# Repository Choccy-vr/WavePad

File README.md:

# WavePad

### Meet WavePad, the ultimate desktop companion.

With inspiration from the Stream Deck, this can do a whole load of things like opening an app, checking system vitals, along with many more things, such as controlling music, focus, etc. You can even create your own app! The possibilities are endless.

### So, how do you control this?

You can do all those things listed above and more, all with a variety of hand gestures or by interacting with a touch screen. By using an IR camera, WavePad can dectect hand gestures even in the dark!

### Features

- All off-the-shelf parts (Except the PCB)

- Gesture Detection (Hand and some finger tracking)

- Built on Raspberry Pi OS 

- Custom Apps (You can build them yourself!)

- Touch Screen

- PC Communication (Acting like a Stream Deck)

- Standalone Operation
  
- More To Come

### BOM

| Item Name    | Purpose           | Source                                                 | Price | Total |
| ------------ | ----------------- | ------------------------------------------------------ | ----- | ----- |
| CM4 1GB Lite | Main Compute Unit | https://www.mouser.com/ProductDetail/358-SC0691        | $35$  |       |
| 4.3in QLED   | Display           | https://www.waveshare.com/43h-800480-ips.htm?sku=24774 | $40$  |       |
| NoIR Camera  | Gesture           | https://www.mouser.com/ProductDetail/358-SC0024        | $15$  |       |
|              |                   |                                                        |       |       |
|              |                   |                                                        |       |       |

## Work in Progress

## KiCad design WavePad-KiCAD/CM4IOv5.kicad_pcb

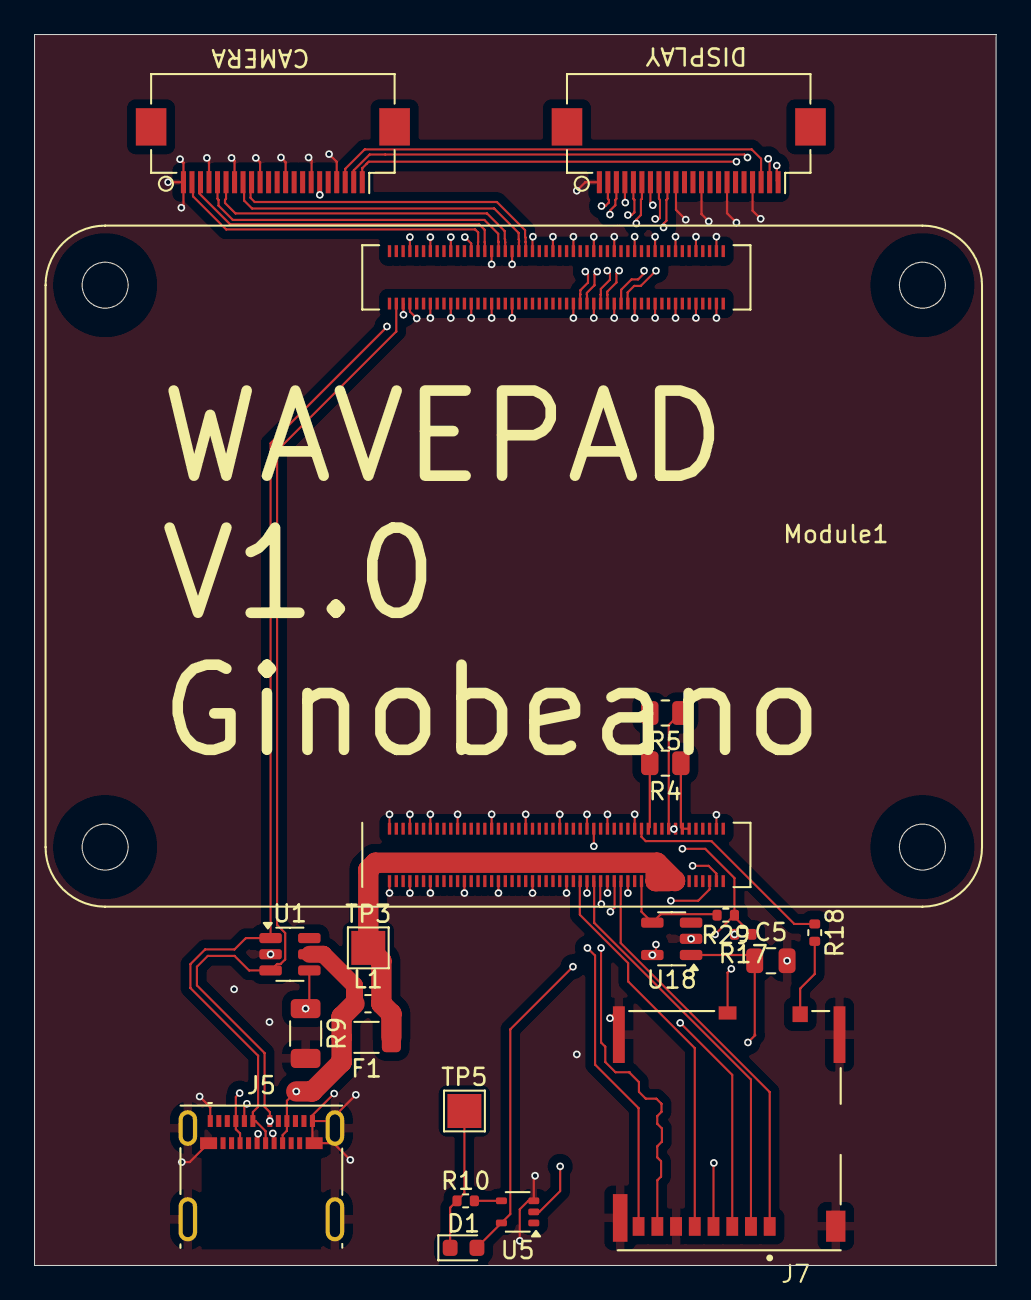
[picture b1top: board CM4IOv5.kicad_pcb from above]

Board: 4 copper layers, 56.5 x 72.3 mm, 21 parts (0 on the bottom side), 39 nets.

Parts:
C5: 10u; C_0805_2012Metric
D1: LED Red; LED_0603_1608Metric
F1: PTC Fuse; R_1206_3216Metric
J5: USB_C_Receptacle_USB2.0_14P; USB_C_Receptacle_Molex_105450-0101
J7: Micro_SD_Card_Det; SDCARD_MOLEX_503398-1892
J8, J15: Conn_01x22_Female; Hirose_FH12-22S-0.5SH_1x22-1MP_P0.50mm_Horizontal
L1: L; L_0603_1608Metric
Module1: ComputeModule4; Raspberry-Pi-4-Compute-Module
R4: nf; R_0805_2012Metric
R5: 0R; R_0805_2012Metric
R9: 5.1K; R_1206_3216Metric
R10: 1k; R_0402_1005Metric
R17, R18: nf; R_0402_1005Metric
R29: 12K 1%; R_0402_1005Metric
TP3: USB 5v; TestPoint_Pad_2.0x2.0mm
TP5: TestPoint; TestPoint_Pad_2.0x2.0mm
U1: USBLC6-4SC6; SOT-23-6
U5: 74LVC1G07SE-7; SOT-353_SC-70-5
U18: RT9742GGJ5; SOT-23-5

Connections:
/+3.3v: D1.2 (A), Module1.84 (+3.3v_(Output)), Module1.86 (+3.3v_(Output)), R5.1, R17.1, R29.1, U5.5 (VCC), U18.5 (IN)
/+5v: F1.1, L1.2, Module1.77 (+5v_(Input)), Module1.79 (+5v_(Input)), Module1.81 (+5v_(Input)), Module1.83 (+5v_(Input)), Module1.85 (+5v_(Input)), Module1.87 (+5v_(Input)), TP3.1
/CM4_GPIO (GPIO, SDCARD)/+1.8v: Module1.88 (+1.8v_(Output)), Module1.90 (+1.8v_(Output)), R4.1
/CM4_GPIO (GPIO, SDCARD)/GPIO_VREF: Module1.78 (GPIO_VREF(1.8v/3.3v_Input)), R4.2, R5.2
/CM4_GPIO (GPIO, SDCARD)/Reserved: Module1.76 (Reserved), R18.1
/CM4_GPIO (GPIO, SDCARD)/SD_CLK: J7.5 (CLK), Module1.57 (SD_CLK)
/CM4_GPIO (GPIO, SDCARD)/SD_CMD: J7.3 (CMD), Module1.62 (SD_CMD)
/CM4_GPIO (GPIO, SDCARD)/SD_DAT0: J7.7 (DAT0), Module1.63 (SD_DAT0)
/CM4_GPIO (GPIO, SDCARD)/SD_DAT1: J7.8 (DAT1), Module1.67 (SD_DAT1)
/CM4_GPIO (GPIO, SDCARD)/SD_DAT2: J7.1 (DAT2), Module1.69 (SD_DAT2)
/CM4_GPIO (GPIO, SDCARD)/SD_DAT3: J7.2 (DAT3/CD), Module1.61 (SD_DAT3)
/CM4_GPIO (GPIO, SDCARD)/SD_PWR: C5.1, J7.4 (VDD), U18.1 (OUT)
/CM4_GPIO (GPIO, SDCARD)/SD_PWR_ON: Module1.75 (SD_PWR_ON), R29.2, U18.4 (EN)
/CM4_GPIO (GPIO, SDCARD)/nPWR_LED: Module1.95 (nPI_LED_PWR), U5.2
/CM4_HighSpeed/+3.3v: J8.22, J15.22
/CM4_HighSpeed/CAM0_C_N: J8.8, Module1.140 (CAM0_C_N)
/CM4_HighSpeed/CAM0_C_P: J8.9, Module1.142 (CAM0_C_P)
/CM4_HighSpeed/CAM0_D0_N: J8.2, Module1.128 (CAM0_D0_N)
/CM4_HighSpeed/CAM0_D0_P: J8.3, Module1.130 (CAM0_D0_P)
/CM4_HighSpeed/CAM0_D1_N: J8.5, Module1.134 (CAM0_D1_N)
/CM4_HighSpeed/CAM0_D1_P: J8.6, Module1.136 (CAM0_D1_P)
/CM4_HighSpeed/CAM_GPIO: J8.17, Module1.97 (Camera_GPIO)
/CM4_HighSpeed/DSI0_C_N: J15.8, Module1.169 (DSI0_C_N)
/CM4_HighSpeed/DSI0_C_P: J15.9, Module1.171 (DSI0_C_P)
/CM4_HighSpeed/DSI0_D0_N: J15.2, Module1.157 (DSI0_D0_N)
/CM4_HighSpeed/DSI0_D0_P: J15.3, Module1.159 (DSI0_D0_P)
/CM4_HighSpeed/DSI0_D1_N: J15.5, Module1.163 (DSI0_D1_N)
/CM4_HighSpeed/DSI0_D1_P: J15.6, Module1.165 (DSI0_D1_P)
/CM4_HighSpeed/SCL1: J8.20, J15.20
/CM4_HighSpeed/SDA1: J8.21, J15.21
/USB/USB D+: J5.A6 (D+), J5.B6 (D+), Module1.105 (USB2_P), U1.1 (I/O1)
/USB/USB D-: J5.A7 (D-), J5.B7 (D-), Module1.103 (USB2_N), U1.3 (I/O2)
GND: C5.2, J5.A1 (GND), J5.A12 (GND), J5.B1 (GND), J5.B12 (GND), J5.S1 (SHIELD), J7.6 (VSS), J7.11 (SHIELD), J8.1, J8.4, J8.7, J8.10, J8.13, J8.16, J8.19, J15.1, J15.4, J15.7, J15.10, J15.13, J15.16, J15.19, Module1.1 (GND), Module1.2 (GND), Module1.7 (GND), Module1.8 (GND), Module1.13 (GND), Module1.14 (GND), Module1.22 (GND), Module1.23 (GND), Module1.32 (GND), Module1.33 (GND), Module1.42 (GND), Module1.43 (GND), Module1.52 (GND), Module1.53 (GND), Module1.59 (GND), Module1.60 (GND), Module1.65 (GND), Module1.66 (GND), Module1.71 (GND), Module1.74 (GND), Module1.98 (GND), Module1.107 (GND), Module1.108 (GND), Module1.113 (GND), Module1.114 (GND), Module1.119 (GND), Module1.120 (GND), Module1.125 (GND), Module1.126 (GND), Module1.131 (GND), Module1.132 (GND), Module1.137 (GND), Module1.138 (GND), Module1.144 (GND), Module1.150 (GND), Module1.155 (GND), Module1.156 (GND), Module1.161 (GND), Module1.162 (GND), Module1.167 (GND), Module1.168 (GND), Module1.173 (GND), Module1.174 (GND), Module1.179 (GND), Module1.180 (GND), Module1.185 (GND), Module1.186 (GND), Module1.191 (GND), Module1.192 (GND), Module1.197 (GND), Module1.198 (GND), R9.2, U1.2 (GND), U5.3 (GND), U18.2 (GND)
unnamed: D1.1 (K), R10.1, TP5.1
unnamed: J5.A5 (CC1), J5.B5 (CC2), R9.1, U1.4 (I/O3)
unnamed: J7.10 (DET_A), R17.2
unnamed: J7.9 (DET_B), R18.2
unnamed: R10.2, U5.4
unnamed: F1.2, J5.A4 (VBUS), J5.A9 (VBUS), J5.B4 (VBUS), J5.B9 (VBUS), L1.1, U1.5 (VBUS)

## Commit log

2025-05-23 Initial Commit
    Add Journal and README
2025-05-23 Add Schematic/PCB Files
    Adapted off of CM4IO Board Template
2025-05-23 Started PCB
    Added CSI and DSI connector as well as a USB C with protected data and Power
2025-05-24 Worked on PCB
    Almost finished the PCB
2025-05-26 Base OS
2025-05-26 Update JOURNAL.md
    5/26
2025-05-28 Fixed OS
2025-06-04 Finish PCB Design
2025-06-04 Specify Serial-Number placement
2025-06-17 Home Screen Layout
2025-06-17 Apps Screen
2025-06-18 Fix Navigation Bug
2025-06-20 Apps
2025-06-21 SQLite Manager
2025-06-23 Pipes
2025-06-23 Pipes & JSON
2025-06-23 Run Pipes and Remove Setup
2025-06-23 Building
2025-06-26 Weather
2025-06-27 Weather service
2025-06-28 Weather UI
2025-06-30 Weather - Home Page
2025-07-02 Weather Details
2025-07-02 Quick UI Change
2025-07-03 Finished Weather App
2025-07-04 Macro Pad App
2025-07-07 OOBE
2025-07-10 Home Stretch
2025-07-10 Pics
2025-07-10 Fixed videos (Thanks @shr)
2025-07-10 Build Apps
2025-07-23 Notifications & Dbus
    It has been quite a while since I committed anyway I finished Notifications and I moved Weather to DBUS instead of WaveDB. Honestly don't know why I didn't start with dbus.
2025-07-23 Fix problem with Weather App
2025-07-24 Update Demo.md
    I don't know why the images went all weird but I fixed them
2025-07-24 Add version of WavePad being reviewed
2025-07-25 Fix grammar
2025-07-27 OnDevice Videos
2025-07-28 Sys_Stats
2025-07-29 Build script
    The build-config right now is just a draft right now.
2025-07-30 wave_tray
2025-07-30 Fix a few things WaveOS
2025-08-06 QEMU
